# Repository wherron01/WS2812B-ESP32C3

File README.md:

# WS2812B-ESP32C3
A simple display driver for a 16x16 WS2812B matrix using the ESP32-C3 microcontroller

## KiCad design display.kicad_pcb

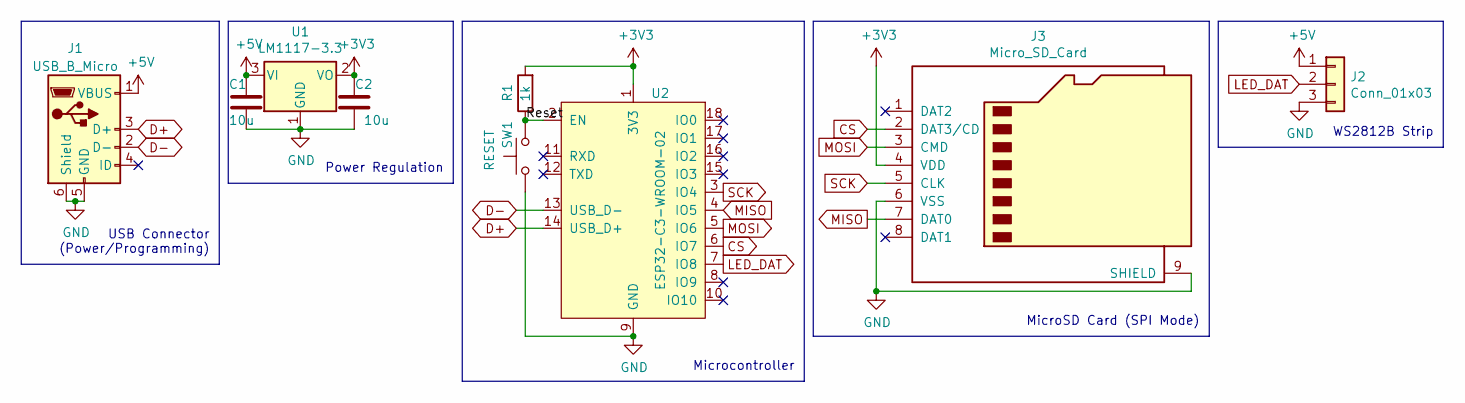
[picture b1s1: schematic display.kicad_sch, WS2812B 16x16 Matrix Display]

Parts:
C1, C2: 10u; C_0805_2012Metric_Pad1.18x1.45mm_HandSolder
J1: USB_B_Micro; USB_Micro-B_Wuerth_629105150521
J2: Conn_01x03; SolderWire-0.5sqmm_1x03_P4.6mm_D0.9mm_OD2.1mm
J3: Micro_SD_Card; microSD_HC_Wuerth_693072010801
R1: 1k; R_0805_2012Metric_Pad1.20x1.40mm_HandSolder
SW1: RESET; SW_SPST_EVQP7C
U1: LM1117-3.3; SOT-223-3_TabPin2
U2: ESP32-C3-WROOM-02; ESP-WROOM-02

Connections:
+3V3: C2.1, J3.4 (VDD), R1.2, U1.2 (VO), U2.1 (3V3)
+5V: C1.1, J1.1 (VBUS), J2.1, U1.3 (VI)
/Reset: R1.1, SW1.2, U2.2 (EN)
CS: J3.2 (DAT3/CD), U2.6 (IO7)
D+: J1.3 (D+), U2.14 (USB_D+)
D-: J1.2 (D-), U2.13 (USB_D-)
GND: C1.2, C2.2, J1.5 (GND), J1.6 (Shield), J2.3, J3.6 (VSS), J3.9 (SHIELD), SW1.1, U1.1 (GND), U2.9 (GND), U2.19 (GND)
LED_DAT: J2.2, U2.7 (IO8)
MISO: J3.7 (DAT0), U2.4 (IO5)
MOSI: J3.3 (CMD), U2.5 (IO6)
SCK: J3.5 (CLK), U2.3 (IO4)

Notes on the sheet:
WS2812B Strip
MicroSD Card (SPI Mode)
Power Regulation
USB Connector (Power/Programming)
Microcontroller

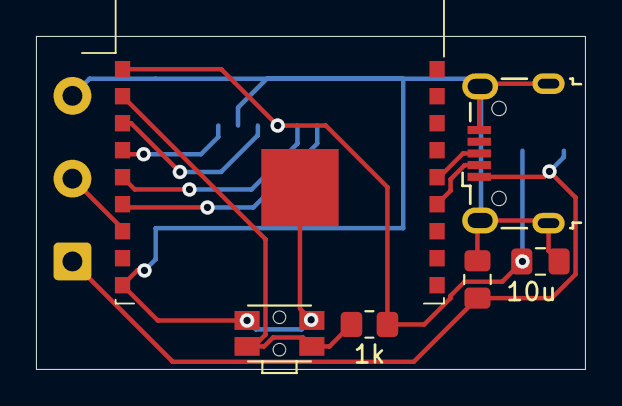
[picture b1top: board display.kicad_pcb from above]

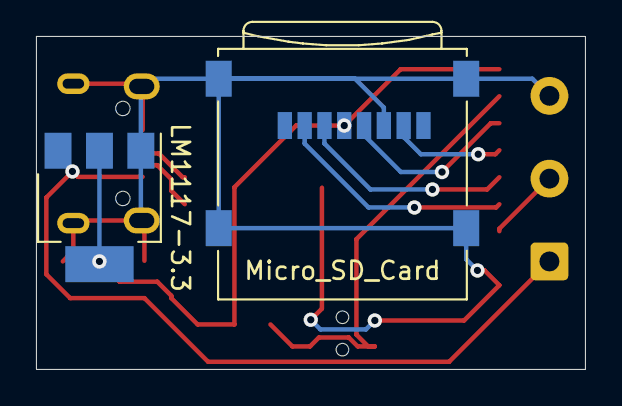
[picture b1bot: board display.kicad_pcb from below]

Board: 2 copper layers, 30.5 x 18.5 mm, 9 parts (2 on the bottom side), 11 nets.

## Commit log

2022-02-15 Initial push
